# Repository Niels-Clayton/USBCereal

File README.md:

# [USBCereal](https://niels-clayton.github.io/USBCereal/)

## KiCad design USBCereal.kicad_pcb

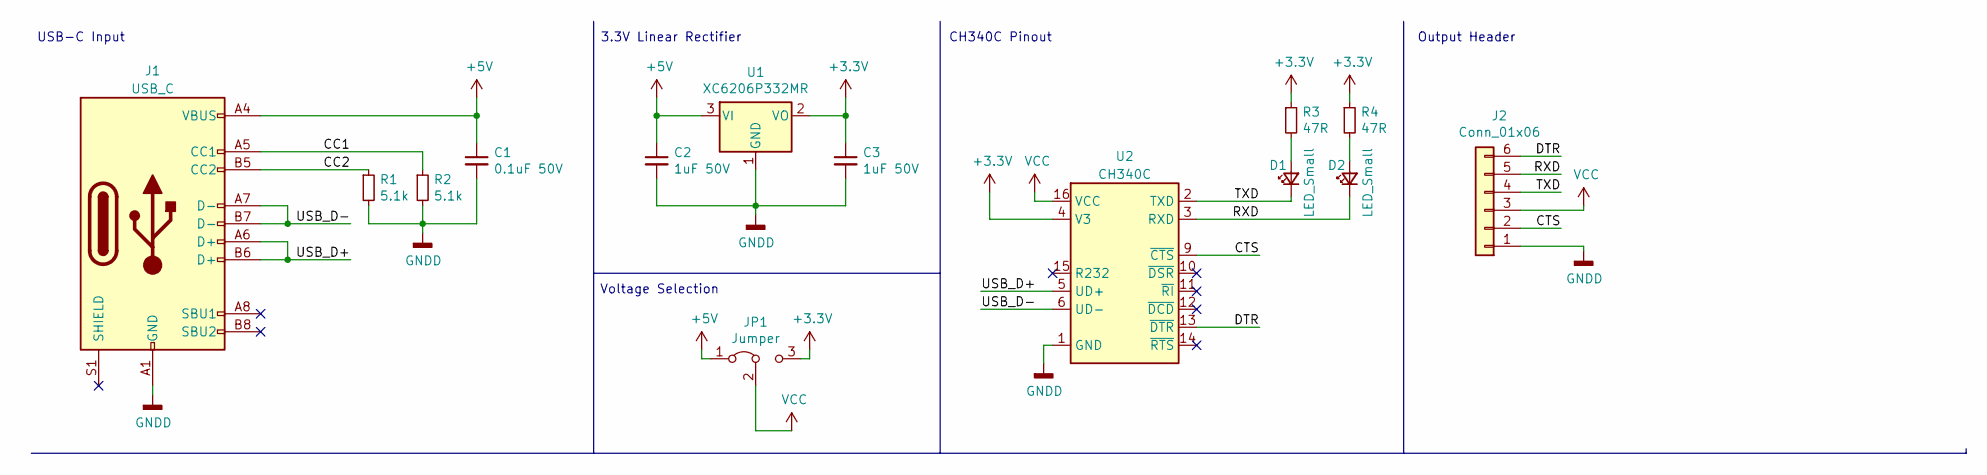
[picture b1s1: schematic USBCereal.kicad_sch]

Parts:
C1: 0.1uF 50V; C_0603_1608Metric_Pad1.08x0.95mm_HandSolder; Part Number CC0603KRX7R9BB104; LCSC CL10A105KB8NNNC
C2, C3: 1uF 50V; C_0603_1608Metric_Pad1.08x0.95mm_HandSolder; Part Number CL10A105KB8NNNC; LCSC CL10A105KB8NNNC
D1, D2: LED_Small; LED_0603_1608Metric_Pad1.05x0.95mm_HandSolder; Part Number 19-217/BHC-ZL1M2RY/3T; LCSC 19-217/BHC-ZL1M2RY/3T
J1: USB_C; USB_C_Receptacle_HRO_TYPE-C-31-M-12; Part Number 2137160001; LCSC C165948
J2: Conn_01x06; PinHeader_1x06_P2.54mm_Horizontal
JP1: Jumper; PinHeader_1x03_P2.54mm_Vertical
R1, R2: 5.1k; R_0603_1608Metric_Pad0.98x0.95mm_HandSolder; Part Number 0603WAF5101T5E; LCSC 0603WAF5101T5E
R3, R4: 47R; R_0603_1608Metric_Pad0.98x0.95mm_HandSolder; Part Number 0603WAF470JT5E; LCSC 0603WAF470JT5E
U1: XC6206P332MR; SOT-23; LCSC C5446
U2: CH340C; SOIC-16_3.9x9.9mm_P1.27mm; LCSC C84681

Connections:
+3V3: C3.1, JP1.3 (B), R3.1, R4.1, U1.2 (VO), U2.4 (V3)
+5V: C1.1, C2.1, J1.A4 (VBUS), J1.A9 (VBUS), J1.B4 (VBUS), J1.B9 (VBUS), JP1.1 (A), U1.3 (VI)
/CC1: J1.A5 (CC1), R2.1
/CC2: J1.B5 (CC2), R1.1
/CTS: J2.2, U2.9 (~CTS)
/DTR: J2.6, U2.13 (~DTR)
/RXD: D2.1 (K), J2.5, U2.3 (RXD)
/TXD: D1.1 (K), J2.4, U2.2 (TXD)
/USB_D+: J1.A6 (D+), J1.B6 (D+), U2.5 (UD+)
/USB_D-: J1.A7 (D-), J1.B7 (D-), U2.6 (UD-)
GNDD: C1.2, C2.2, C3.2, J1.A1 (GND), J1.A12 (GND), J1.B1 (GND), J1.B12 (GND), J2.1, R1.2, R2.2, U1.1 (GND), U2.1 (GND)
unnamed: D1.2 (A), R3.2
unnamed: D2.2 (A), R4.2
VCC: J2.3, JP1.2 (C), U2.16 (VCC)

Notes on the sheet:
Output Header
CH340C Pinout
Voltage Selection
USB-C Input
3.3V Linear Rectifier

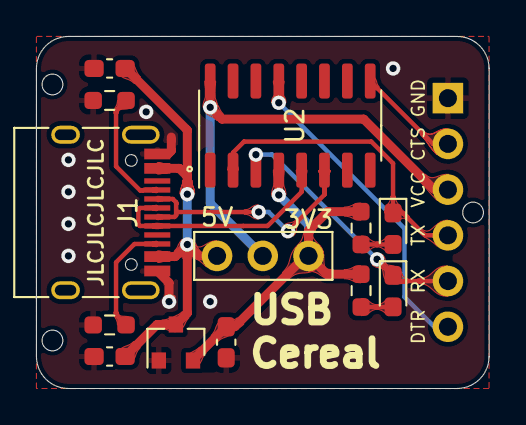
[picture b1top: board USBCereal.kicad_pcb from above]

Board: 2 copper layers, 25.1 x 19.6 mm, 14 parts (0 on the bottom side), 14 nets.

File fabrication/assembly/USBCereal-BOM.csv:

Comment,Designator,Footprint,LCSC
0.1uF  50V,C1,Capacitor_SMD:C_0603_1608Metric_Pad1.08x0.95mm_HandSolder,CC0603KRX7R9BB104
1uF  50V,"C2,C3",Capacitor_SMD:C_0603_1608Metric_Pad1.08x0.95mm_HandSolder,CL10A105KB8NNNC
LED_Small,"D1,D2",LED_SMD:LED_0603_1608Metric_Pad1.05x0.95mm_HandSolder,19-217/BHC-ZL1M2RY/3T
USB_C,J1,Connector_USB:USB_C_Receptacle_HRO_TYPE-C-31-M-12,C165948
5.1k,"R1,R2",Resistor_SMD:R_0603_1608Metric_Pad0.98x0.95mm_HandSolder,0603WAF5101T5E
47R,"R3,R4",Resistor_SMD:R_0603_1608Metric_Pad0.98x0.95mm_HandSolder,0603WAF470JT5E
SW_SPDT,SW1,Button_Switch_SMD:SW_SPDT_CK-JS102011SAQN,C128953
XC6206P332MR,U1,Package_TO_SOT_SMD:SOT-23,C5446
CH340C,U2,Package_SO:SOIC-16_3.9x9.9mm_P1.27mm,C84681

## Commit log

2021-06-22 create project
2021-06-23 ifxed the footprints
2021-06-25 First schematic complete using the CH340C
2021-06-26 Complete schematic, Begin on PCB placment and design
2021-06-26 Complete the PCB, ficed spelling errors
2021-06-26 update schematic
2021-06-27 Add logo
2021-06-28 Finished PCB, generated fabrication files
2021-06-28 fix conflicts
2021-06-29 update non-connecting traces, rebuild gerber's
2021-06-29 re-package gerber
2021-06-29 fixed silk screen issue and updated gerbers
2021-06-29 finalise fabrication files, read for JLCPCB order
2021-07-17 update removing extra trace
2021-07-18 Redsigned the pcb to use a switch rather than a jumper for the selection of the supply voltage
2021-07-18 update logo placment
2021-07-18 update pcb layout
2021-07-19 rebuild ground plain
2021-11-14 fixed the copper pours, and removed unnecessary copper
2021-11-15 generate the interactive BOM
2021-11-15 update libraries and generate the ibom
